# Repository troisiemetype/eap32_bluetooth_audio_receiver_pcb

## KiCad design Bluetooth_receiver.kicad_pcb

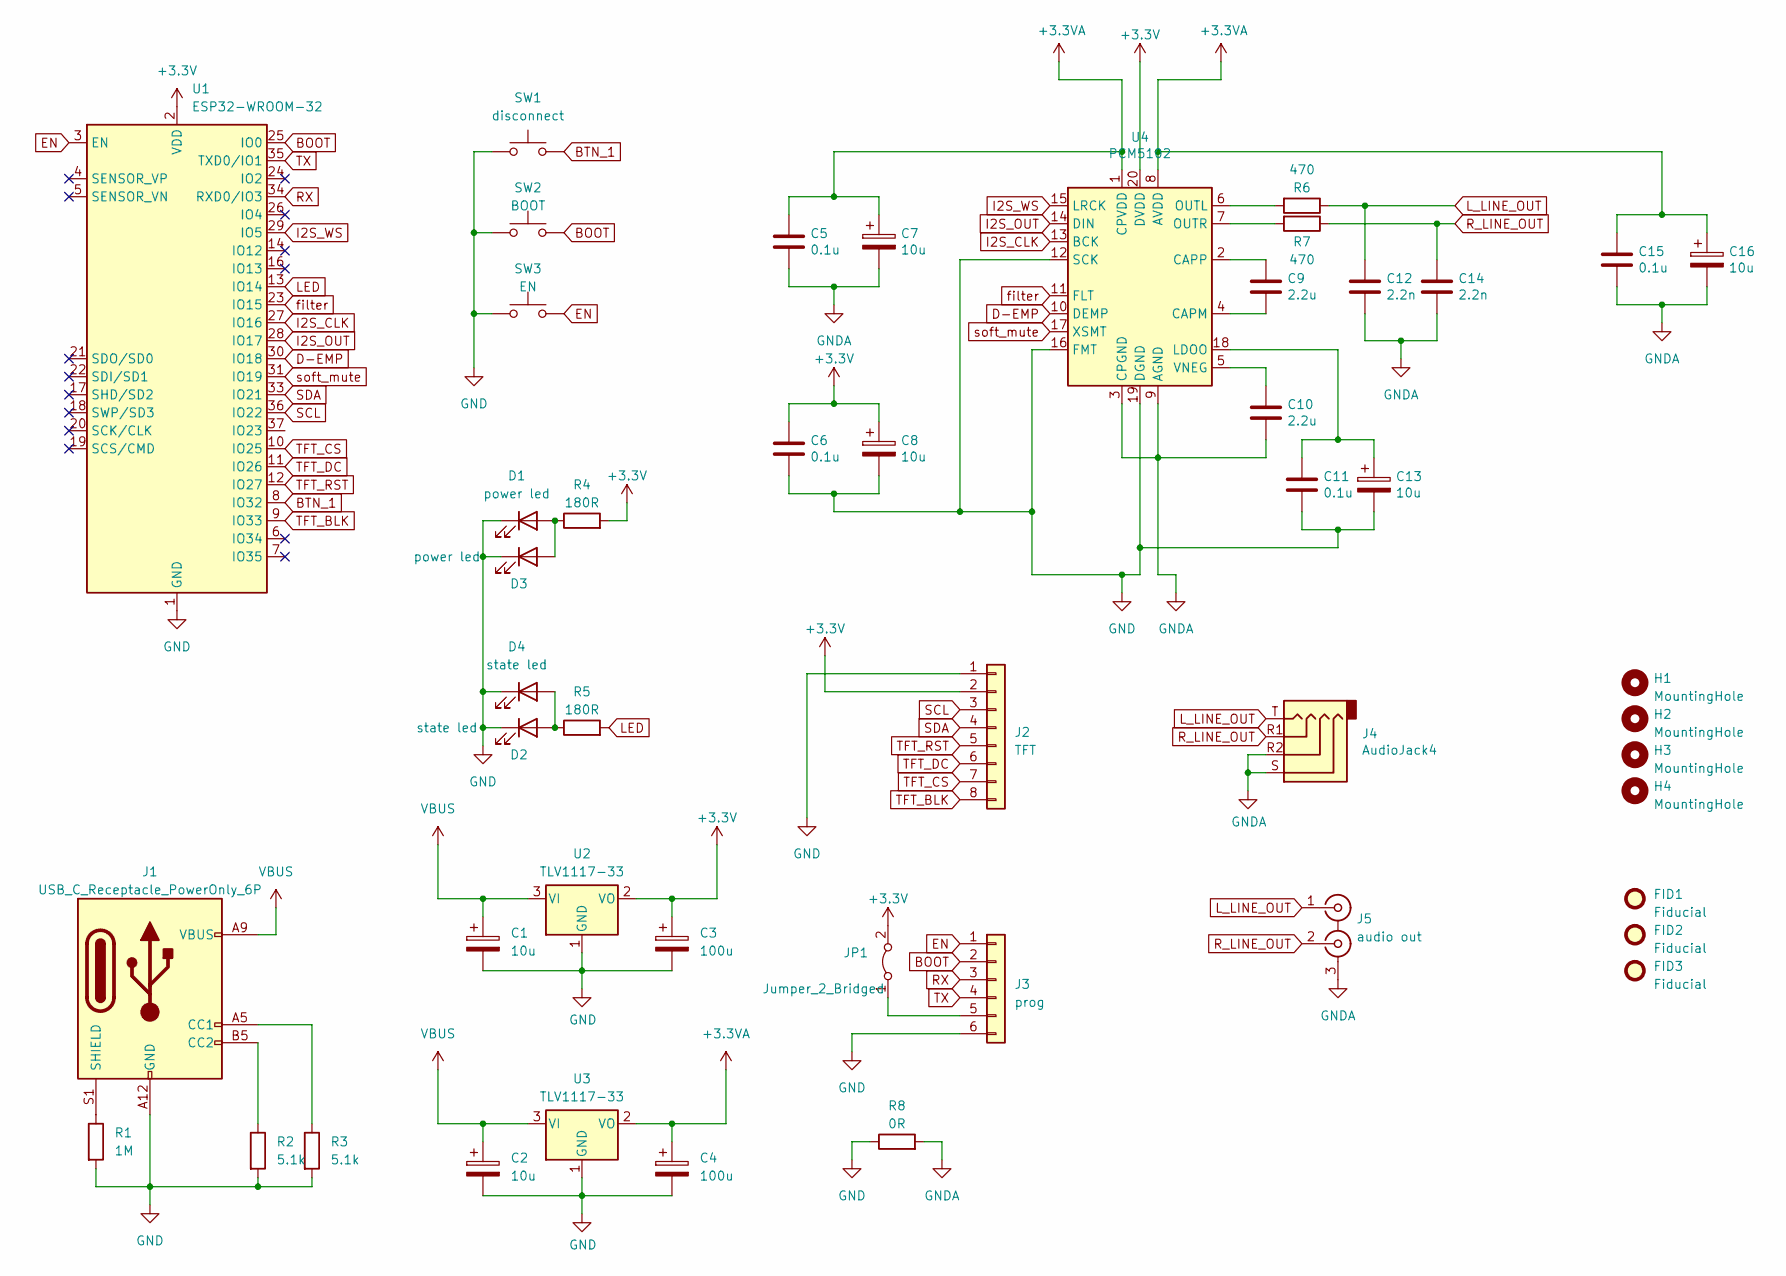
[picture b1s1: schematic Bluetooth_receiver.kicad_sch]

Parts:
C1, C2, C7, C8, C13, C16: 10u; CP_Elec_4x5.4
C3, C4: 100u; CP_Elec_6.3x5.4
C5, C6, C11, C15: 0.1u; C_0603_1608Metric
C9, C10: 2.2u; C_0603_1608Metric
C12, C14: 2.2n; C_0603_1608Metric
D1: power led; LED_D3.0mm
D2: state led; LED_D3.0mm
D3: power led; LED_0805_2012Metric
D4: state led; LED_0805_2012Metric
FID1, FID2, FID3: Fiducial; Fiducial_1.5mm_Mask3mm
H1, H2, H3, H4: MountingHole; MountingHole_3.2mm_M3
J1: USB_C_Receptacle_PowerOnly_6P; USB_C_Receptacle_GCT_USB4125-GF-A_6P_THMnt_Horizontal
J2: TFT; PinHeader_1x08_P2.54mm_Vertical
J3: prog; PinHeader_1x06_P2.54mm_Vertical
J4: AudioJack4; Jack_3.5mm_PJ320D_Horizontal
J5: audio out; KOBICONN_156-4218E_4220E_dual_phono_jack
JP1: Jumper_2_Bridged; SolderJumper-2_P1.3mm_Bridged_RoundedPad1.0x1.5mm
R1: 1M; R_0603_1608Metric
R2, R3: 5.1k; R_0603_1608Metric
R4, R5: 180R; R_0603_1608Metric
R6, R7: 470; R_0603_1608Metric
R8: 0R; R_1206_3216Metric
SW1: disconnect; SW_Tactile_SPST_Angled_PTS645Vx39-2LFS
SW2: BOOT; SW_Tactile_SPST_Angled_PTS645Vx39-2LFS
SW3: EN; SW_Push_1P1T_NO_6x6mm_H9.5mm
U1: ESP32-WROOM-32
U2, U3: TLV1117-33; SOT-223-3_TabPin2
U4: PCM5102; TSSOP-20_4.4x6.5mm_P0.65mm

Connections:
+3.3V: C3.1, C6.1, C8.1, J2.2, JP1.2 (B), R4.2, U1.2 (VDD), U2.2 (VO), U4.20 (DVDD)
+3.3VA: C4.1, C5.1, C7.1, C15.1, C16.1, U3.2 (VO), U4.1 (CPVDD), U4.8 (AVDD)
BOOT: J3.2, SW2.2, U1.25 (IO0)
BTN_1: SW1.2, U1.8 (IO32)
D-EMP: U1.30 (IO18), U4.10 (DEMP)
EN: J3.1, SW3.2, U1.3 (EN)
GND: C1.2, C2.2, C3.2, C4.2, C6.2, C8.2, C11.2, C13.2, D1.1 (K), D2.1 (K), D3.1 (K), D4.1 (K), J1.A12 (GND), J1.B12 (GND), J2.1, J3.6, R1.2, R2.2, R3.2, R8.1, SW1.1, SW2.1, SW3.1, U1.1 (GND), U1.15 (GND), U1.38 (GND), U1.39 (GND), U2.1 (GND), U3.1 (GND), U4.12 (SCK), U4.16 (FMT), U4.19 (DGND)
GNDA: C5.2, C7.2, C10.2, C12.2, C14.2, C15.2, C16.2, J4.R2, J4.S, J5.3 (EXT), R8.2, U4.3 (CPGND), U4.9 (AGND)
I2S_CLK: U1.27 (IO16), U4.13 (BCK)
I2S_OUT: U1.28 (IO17), U4.14 (DIN)
I2S_WS: U1.29 (IO5), U4.15 (LRCK)
LED: R5.2, U1.13 (IO14)
L_LINE_OUT: C12.1, J4.T, J5.1 (IN1), R6.1
unnamed: D1.2 (A), D3.2 (A), R4.1
unnamed: D2.2 (A), D4.2 (A), R5.1
unnamed: J1.A5 (CC1), R3.1
unnamed: J1.B5 (CC2), R2.1
unnamed: J1.S1 (SHIELD), R1.1
unnamed: J3.5, JP1.1 (A)
unnamed: C9.2, U4.4 (CAPM)
unnamed: C9.1, U4.2 (CAPP)
unnamed: C11.1, C13.1, U4.18 (LDOO)
unnamed: R6.2, U4.6 (OUTL)
unnamed: R7.2, U4.7 (OUTR)
unnamed: C10.1, U4.5 (VNEG)
RX: J3.3, U1.34 (RXD0/IO3)
R_LINE_OUT: C14.1, J4.R1, J5.2 (IN2), R7.1
SCL: J2.3, U1.36 (IO22)
SDA: J2.4, U1.33 (IO21)
TFT_BLK: J2.8, U1.9 (IO33)
TFT_CS: J2.7, U1.10 (IO25)
TFT_DC: J2.6, U1.11 (IO26)
TFT_RST: J2.5, U1.12 (IO27)
TX: J3.4, U1.35 (TXD0/IO1)
VBUS: C1.1, C2.1, J1.A9 (VBUS), J1.B9 (VBUS), U2.3 (VI), U3.3 (VI)
filter: U1.23 (IO15), U4.11 (FLT)
soft_mute: U1.31 (IO19), U4.17 (XSMT)

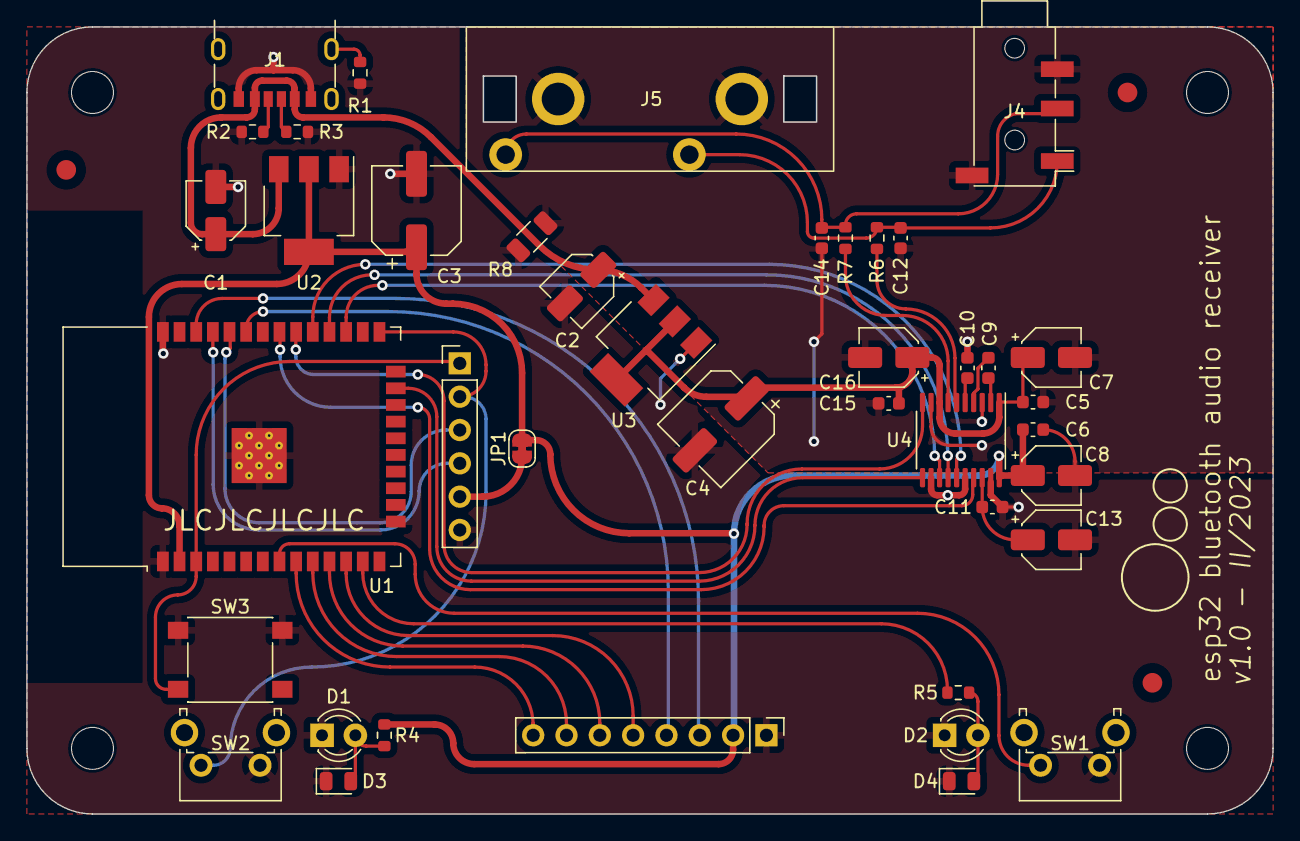
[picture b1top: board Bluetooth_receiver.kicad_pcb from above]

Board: 2 copper layers, 95.0 x 60.0 mm, 48 parts (0 on the bottom side), 37 nets.

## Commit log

2023-02-21 Initial commit. Sent to fabrication.
